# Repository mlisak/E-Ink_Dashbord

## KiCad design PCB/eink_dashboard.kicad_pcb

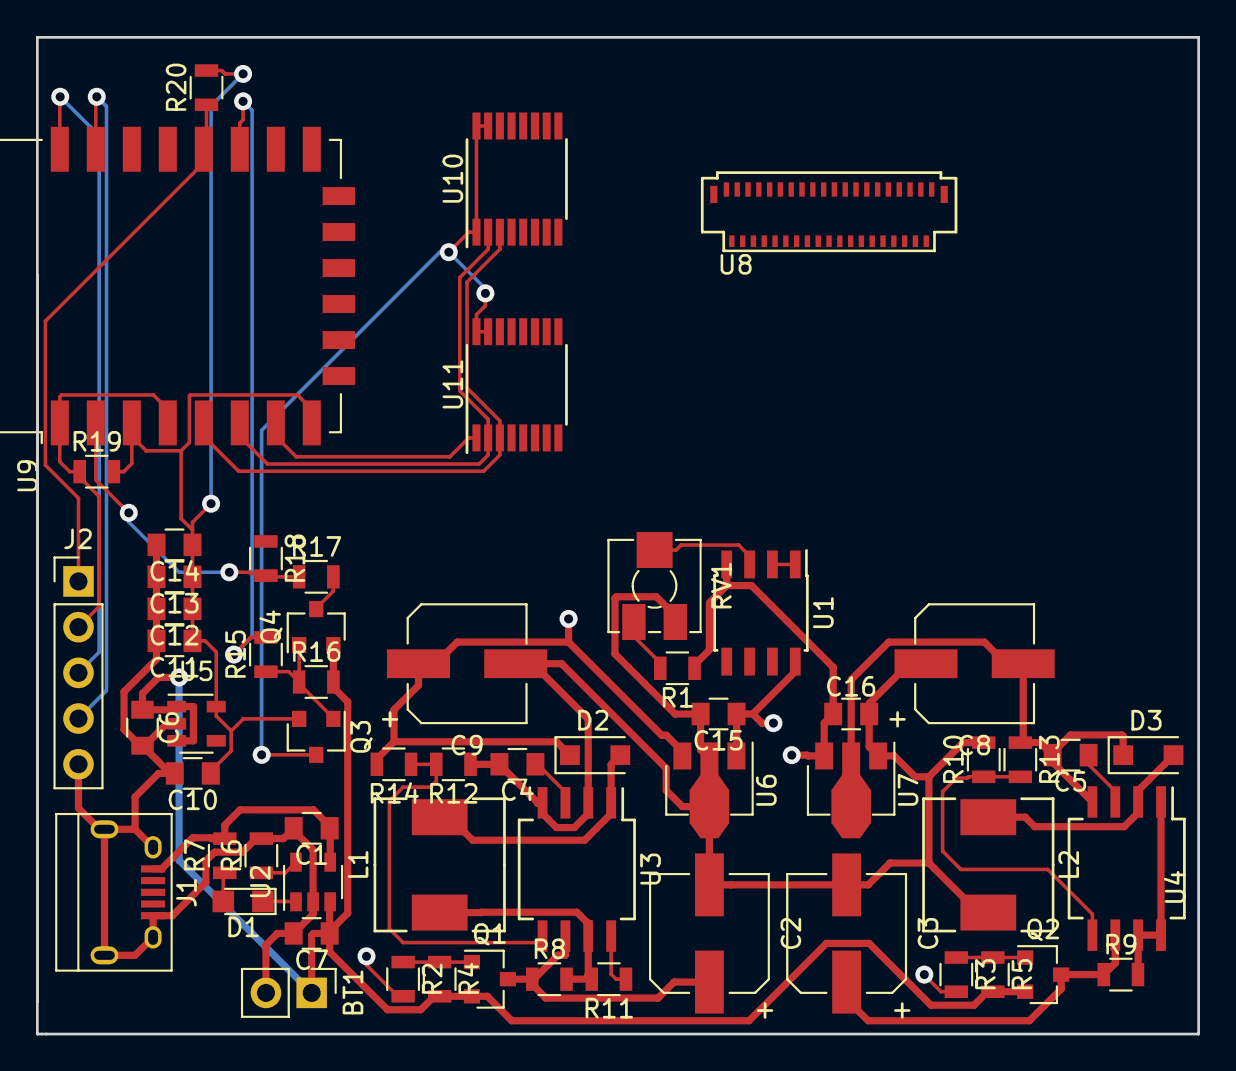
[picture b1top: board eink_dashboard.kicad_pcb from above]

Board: 2 copper layers, 64.5 x 55.4 mm, 60 parts (0 on the bottom side), 56 nets.

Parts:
BT1: Battery_Cell; Pin_Header_Straight_1x02_Pitch2.54mm
C1, C7: 4.7u; C_0805
C2, C3, C8, C9: 47u; CP_Elec_6.3x5.3
C4, C5: 680p; C_0805
C6, C10: 1u; C_0805
C11, C12, C13, C14, C15, C16: 100n; C_0805
D1: LED; LED_0805
D2, D3: SS24; D_SOD-123F
J1: USB_B_Micro; USB_Micro-B
J2: Conn_01x05; Pin_Header_Straight_1x05_Pitch2.54mm
L1, L2: 68 uH; Inductor_Wurth_HCM-7050
Q1, Q2, Q3, Q4: IRLML6402; SOT-23
R1, R4, R5: 47k; R_0805
R2, R3, R15: 10; R_0805
R6: TBD; R_0805
R7: 470; R_0805
R8, R9: 0.39; R_0805
R10: 15k; R_0805
R11: 180; R_0805
R12: 1.2k; R_0805
R13: 1k; R_0805
R14: 20k; R_0805
R16: 47K; R_0805
R17: 33k; R_0805
R18, R19, R20: 10k; R_0805
RV1: 10k; Potentiometer_Trimmer_Vishay_TS53YJ
U1: LM358; SOIC-8_3.9x4.9mm_Pitch1.27mm
U2: MCP73831; SOT-23-5
U3, U4: MC34063; SO-8_5.3x6.2mm_Pitch1.27mm
U5: MIC5504-3.3YM5; SOT-23-5
U6: L78L15; SOT-89-3
U7: L79L15; SOT-89-3
U8: ED060SC4
U9: ESP-12F; ESP-12E
U10, U11: CD4094; TSSOP-16_4.4x5mm_Pitch0.65mm

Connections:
+3V3: C10.1, C11.1, C12.1, C13.1, C14.1, Q3.2, R19.2, R20.2, U5.5, U9.3, U9.8
+15V: C15.1, U1.8, U6.1, U8.2
+22V: C9.1, D2.1, R14.2, U6.3, U8.23
+BATT: BT1.1, C6.1, C7.1, Q1.2, Q2.2, Q4.2, R4.2, R5.2, R16.2, U2.3, U5.1, U5.3
-15V: C16.1, R1.1, U1.4, U7.3, U8.1
-20V: C5.2, C8.2, D3.1, R13.1, U4.4, U7.2, U8.24
CKV: U8.33, U8.38, U11.7
CL: U8.5, U9.20
CLK: U9.5, U10.3, U11.3
D: U9.6, U10.2, U11.2
EINK_EN: R15.2, U9.17
EINK_VDD: Q3.3, U8.4, U8.30, U8.35, U8.36, U10.1, U10.15, U10.16, U11.15, U11.16
GMODE: U8.27, U8.28, U11.6
GND: BT1.2, C1.2, C2.2, C3.2, C4.2, C6.2, C7.2, C8.1, C9.2, C10.2, C11.2, C12.2, C13.2, C14.2, C15.2, C16.2, J1.5, J1.6, J2.5, L2.2, R6.2, R10.2, R12.1, R18.1, RV1.1, U2.2, U3.2, U3.4, U5.2, U6.2, U7.1, U8.3, U8.8, U8.29, U8.31, U8.34, U9.15, U10.8, U11.8
LE: U8.6, U11.13
NEG_EN: R3.2, U11.4
unnamed: C1.1, J1.1, R7.2, U2.4
unnamed: C2.1, Q1.3, R8.1, U3.6
unnamed: C3.1, Q2.3, R9.1, U4.6
unnamed: C4.1, U3.3
unnamed: C5.1, U4.3
unnamed: D1.1, U2.1
unnamed: D1.2, R7.1
unnamed: D2.2, L1.2, U3.1
unnamed: D3.2, L2.1, U4.2
unnamed: J2.1, R20.1, U9.18
unnamed: J2.3, U9.22
unnamed: J2.4, U9.21
unnamed: L1.1, R8.2, R11.2, U3.7
unnamed: Q1.1, R2.1, R4.1
unnamed: Q2.1, R3.1, R5.1
unnamed: Q3.1, Q4.1, R15.1, R16.1
unnamed: Q4.3, R17.2
unnamed: R1.2, RV1.3
unnamed: R6.1, U2.5
unnamed: R9.2, U4.1, U4.7, U4.8
unnamed: R10.1, R13.2, U4.5
unnamed: R11.1, U3.8
unnamed: R12.2, R14.1, U3.5
unnamed: R17.1, R18.2, U9.2
unnamed: RV1.2, U1.3
unnamed: U8.12, U10.4
unnamed: U8.13, U10.5
unnamed: U8.14, U10.6
unnamed: U8.15, U10.7
unnamed: U8.19, U10.11
unnamed: U8.18, U10.12
unnamed: U8.17, U10.13
unnamed: U8.16, U10.14
OE: U8.7, U9.19
POS_EN: R2.2, U11.5
SPH: U8.11, U11.12
SPV: U8.32, U8.37, U11.14
STR: U9.7, U11.1
VCOM: U1.1, U1.2, U8.22
~RST: J2.2, R19.1, U9.1, U9.4

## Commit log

2019-04-25 IMPORTANT FIX: D3 direction switched
2019-04-25 Separated R15/R16 name fields
2019-04-25 PCB design project created
2019-04-25 Schematic annotated, netlist generated
    *.net files added to .gitignore
2019-04-25 Control circuitry added
2019-04-25 CD4094 symbol added
2019-04-25 Added *.bck files to .gitignore
2019-04-25 Pulled ADC and EINK_VDD mosfets to +BATT instead of +3.3V
2019-04-25 Fixed schematic to use correct SPI pins on ESP-12F
2019-04-25 IMPORTANT FIX: D and STR swapped on ESP module
2019-04-25 Routed separate sections of PCB
2019-04-25 Added +/-15V linear regulators
2019-04-25 Initial firmware files created
2019-04-25 SPI initialization added
2019-04-25 Changed EINK_EN to GPIO15 (was GPIO2)
    This is to not interfere with LED present on ESP12 modules
2019-04-25 BOM catalog added to .gitignore
2019-04-25 Working files added to .gitignore
2019-04-25 Firmware directory added
    ESP8266_RTOS_SDK submodule and makefile added
2019-04-25 Silkscreen labels placed in better positions
2019-04-25 Symbol cache added to .gitignore
2019-04-25 Added footprint library for ED060SC4 E-ink display
2019-04-25 +22V and -20V generation circuitry added
2019-04-25 GPIO initialization added
2019-04-25 Added symbol library for ED060SC4 E-ink display
2019-04-25 Removed SPI event callback
2019-04-25 PCB mostly routed
    Final board layout defined
2019-04-25 Footprints assigned to elements
    Components values tweaked to match available products
2019-04-25 STR and D pins swapped for better routing
2019-04-25 Added *.bak files to .gitignore
2019-04-25 Finished routing board
2019-04-25 Battery charging circuitry added
2019-04-25 Swapped LD3985 LDO regulator to MIC5504
2019-04-25 Renamed custom libraries
2019-04-25 Shift registers moved farther apart
2019-04-25 Placed resistors values inside symbols
2019-04-25 Added opamp to generate adjustabe VCOM
2019-04-25 Ground pours tweaked
    Added pour keepout areas (F.Cu) under ICs, inductors and FPC connector
    Pour minimal width increased
2019-04-25 Placed actual battery symbol instead of connector
2019-04-25 Mitsudomoe symbol and board title added on silkscreen
2019-04-25 3.3V LDO regulator added
2019-04-25 R6 changed to 2k
2019-04-25 Plots folder added to .gitignore
2019-04-25 Tight clearances cleaned up
2019-04-25 SPI transmit implemented
    Writing data (D0~D7) to E-Ink module implemented
2019-04-25 IO initialization tweaked
    SPI clock changed to 2 MHz
    EINK_EN set high aftter init
2019-04-25 Shift register extended IO implemented
